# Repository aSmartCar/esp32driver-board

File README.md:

# ESP32Driver

This project is part of the ASV system and includes the custom PCB

## Specs
- Powersupply: 5.5 V - 36 V (depends on the voltage resistors)
- Microcontroller: ESP32
- USB to UART: FTDI FT231XQ
- Motorcontroller: Sparkfun DUALTB6612FNG

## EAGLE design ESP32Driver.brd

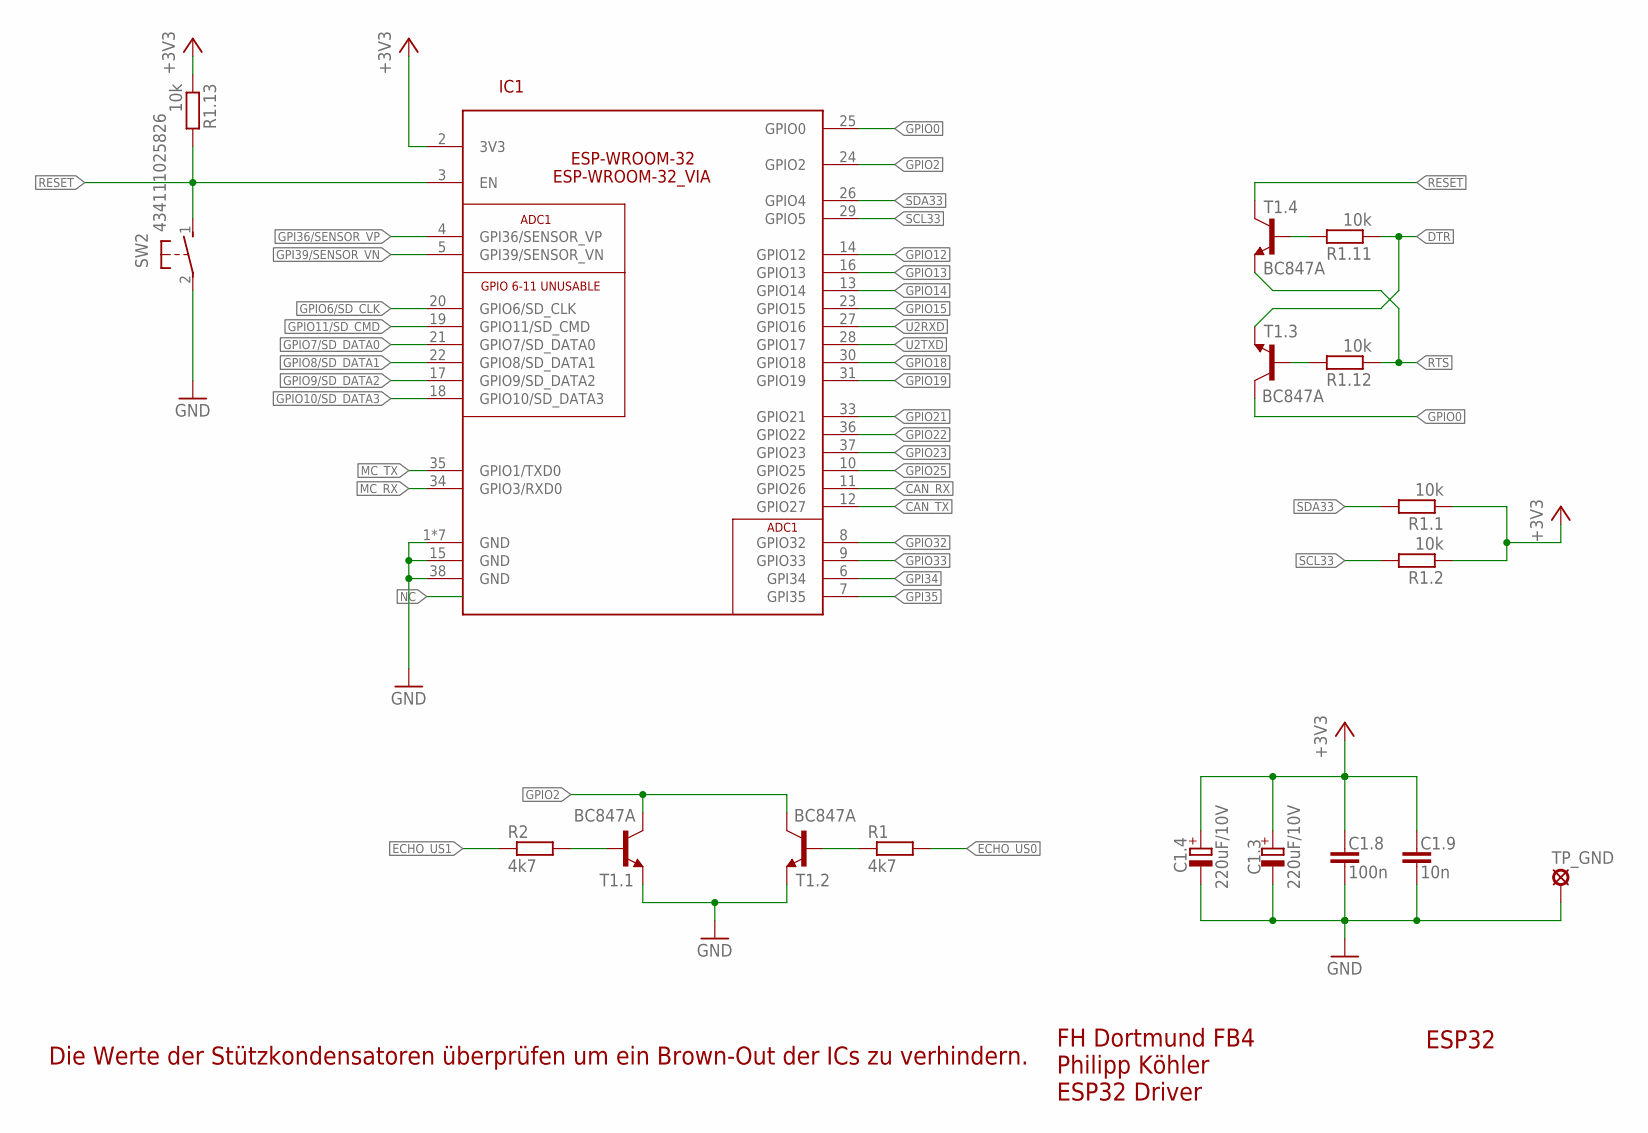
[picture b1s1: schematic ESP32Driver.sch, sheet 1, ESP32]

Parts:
C1.3, C1.4: 220uF/10V; SMC_C
C1.8: 100n; C0805
C1.9: 10n; C0805
IC1: ESP-WROOM-32_VIA; ESP-WROOM-32-VIA
R1, R2: 4k7; R0603
R1.1, R1.2, R1.11, R1.12, R1.13: 10k; R0805
SW2: 434111025826; 434121025816
T1.1, T1.2, T1.3, T1.4: BC847A; SOT23
TP_GND: GND; LSP10

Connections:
+3V3: C1.3.+, C1.4.+, C1.8.1, C1.9.1, IC1.2 (3V3), R1.1.1, R1.2.1, R1.13.1; also elsewhere on the board
CAN_RX: IC1.11 (GPIO26); also elsewhere on the board
CAN_TX: IC1.12 (GPIO27); also elsewhere on the board
DTR: R1.11.1, T1.3.2 (E); also elsewhere on the board
ECHO_US0: R1.2; also elsewhere on the board
ECHO_US1: R2.1; also elsewhere on the board
GND: C1.3.-, C1.4.-, C1.8.2, C1.9.2, IC1.1 (GND), IC1.15 (GND), IC1.38 (GND), IC1.THERMAL (GND), IC1.THERMAL1 (GND), IC1.T_VIA1 (GND), IC1.T_VIA2 (GND), IC1.T_VIA3 (GND), IC1.T_VIA4 (GND), SW2.2, T1.1.2 (E), T1.2.2 (E), TP_GND.MP; also elsewhere on the board
GPI34: IC1.6 (GPI34); also elsewhere on the board
GPI35: IC1.7 (GPI35); also elsewhere on the board
GPI36/SENSOR_VP: IC1.4 (GPI36/SENSOR_VP); also elsewhere on the board
GPI39/SENSOR_VN: IC1.5 (GPI39/SENSOR_VN); also elsewhere on the board
GPIO0: IC1.25 (GPIO0), T1.3.3 (C); also elsewhere on the board
GPIO2: IC1.24 (GPIO2), T1.1.3 (C), T1.2.3 (C)
GPIO6/SD_CLK: IC1.20 (GPIO6/SD_CLK)
GPIO7/SD_DATA0: IC1.21 (GPIO7/SD_DATA0)
GPIO8/SD_DATA1: IC1.22 (GPIO8/SD_DATA1)
GPIO9/SD_DATA2: IC1.17 (GPIO9/SD_DATA2)
GPIO10/SD_DATA3: IC1.18 (GPIO10/SD_DATA3)
GPIO11/SD_CMD: IC1.19 (GPIO11/SD_CMD)
GPIO12: IC1.14 (GPIO12); also elsewhere on the board
GPIO13: IC1.16 (GPIO13); also elsewhere on the board
GPIO14: IC1.13 (GPIO14); also elsewhere on the board
GPIO15: IC1.23 (GPIO15); also elsewhere on the board
GPIO18: IC1.30 (GPIO18); also elsewhere on the board
GPIO19: IC1.31 (GPIO19); also elsewhere on the board
GPIO21: IC1.33 (GPIO21); also elsewhere on the board
GPIO22: IC1.36 (GPIO22); also elsewhere on the board
GPIO23: IC1.37 (GPIO23); also elsewhere on the board
GPIO25: IC1.10 (GPIO25); also elsewhere on the board
GPIO32: IC1.8 (GPIO32); also elsewhere on the board
GPIO33: IC1.9 (GPIO33); also elsewhere on the board
MC_RX: IC1.34 (GPIO3/RXD0); also elsewhere on the board
MC_TX: IC1.35 (GPIO1/TXD0); also elsewhere on the board
unnamed: R1.1, T1.2.1 (B)
unnamed: R2.2, T1.1.1 (B)
unnamed: R1.12.2, T1.3.1 (B)
unnamed: R1.11.2, T1.4.1 (B)
NC: IC1.32 (NC)
RESET: IC1.3 (EN), R1.13.2, SW2.1, T1.4.3 (C)
RTS: R1.12.1, T1.4.2 (E); also elsewhere on the board
SCL33: IC1.29 (GPIO5), R1.2.2; also elsewhere on the board
SDA33: IC1.26 (GPIO4), R1.1.2; also elsewhere on the board
U2RXD: IC1.27 (GPIO16); also elsewhere on the board
U2TXD: IC1.28 (GPIO17); also elsewhere on the board

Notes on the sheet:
Die Werte der Stützkondensatoren überprüfen um ein Brown-Out der ICs zu verhindern.
GPIO 6-11 UNUSABLE
ESP32
FH Dortmund FB4 Philipp Köhler ESP32 Driver
ADC1

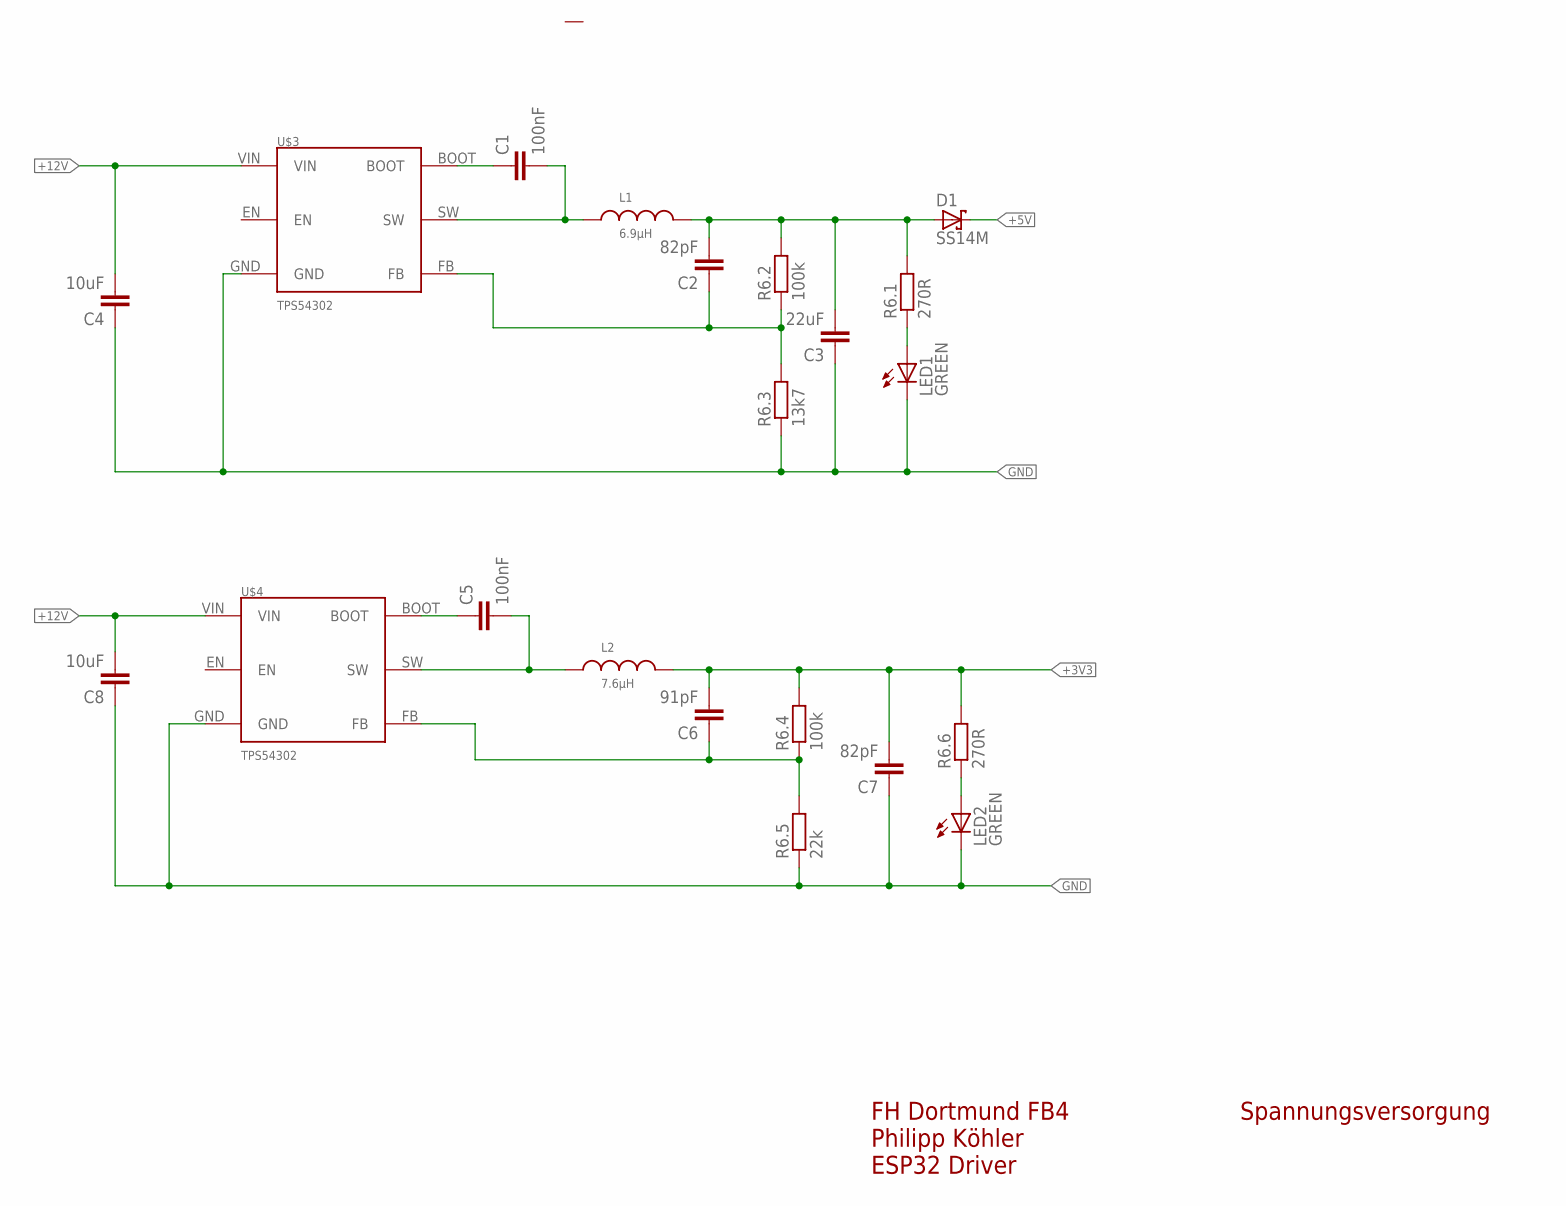
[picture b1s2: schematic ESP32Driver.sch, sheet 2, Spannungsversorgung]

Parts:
C1, C5: 100nF; C0805
C2, C7: 82pF; C0805
C3: 22uF; C0805
C4, C8: 10uF; C0805
C6: 91pF; C0805
D1: SS14M; MICRO-SMA
L1: 6.9µH; WE-HCI_7030/7040/7050
L2: 7.6µH; WE-HCI_7030/7040/7050
LED1, LED2: GREEN; SML0805
R6.1, R6.6: 270R; R0805
R6.2, R6.4: 100k; R0805
R6.3: 13k7; R0805
R6.5: 22k; R0805
U$3, U$4: TPS54302; SOT95P280X110-6

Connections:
+3V3: C6.2, C7.2, L2.2, R6.4.2, R6.6.2; also elsewhere on the board
+5V: D1.1 (C); also elsewhere on the board
+12V: C4.2, C8.2, U$3.VIN, U$4.VIN; also elsewhere on the board
GND: C3.1, C4.1, C7.1, C8.1, LED1.C, LED2.C, R6.3.1, R6.5.1, U$3.GND, U$4.GND; also elsewhere on the board
unnamed: C2.2, C3.2, D1.2 (A), L1.2, R6.1.2, R6.2.2
unnamed: C1.1, U$3.BOOT
unnamed: C1.2, L1.1, U$3.SW
unnamed: C2.1, R6.2.1, R6.3.2, U$3.FB
unnamed: C5.1, U$4.BOOT
unnamed: LED1.A, R6.1.1
unnamed: C5.2, L2.1, U$4.SW
unnamed: C6.1, R6.4.1, R6.5.2, U$4.FB
unnamed: LED2.A, R6.6.1

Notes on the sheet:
Spannungsversorgung
FH Dortmund FB4 Philipp Köhler ESP32 Driver

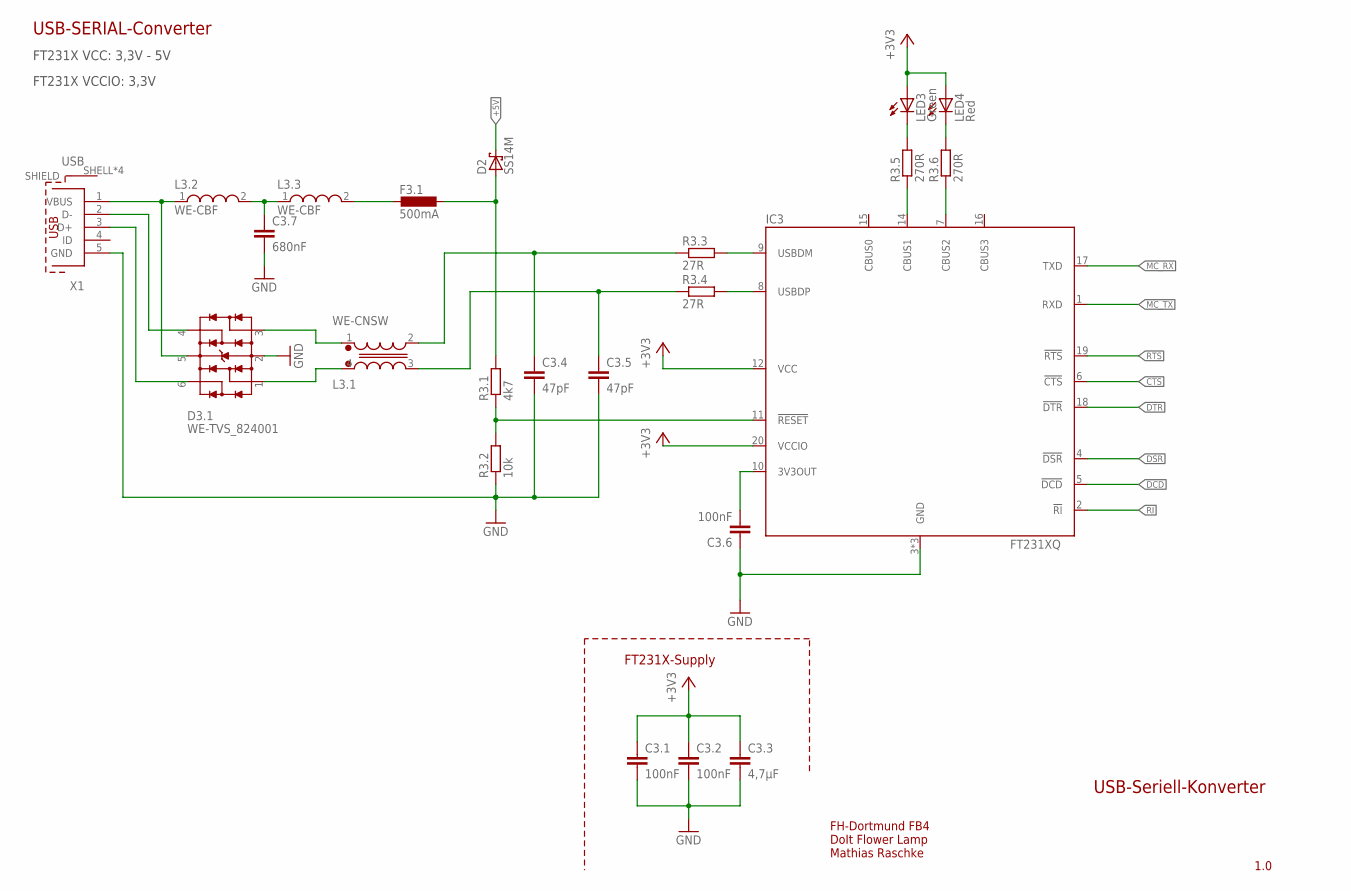
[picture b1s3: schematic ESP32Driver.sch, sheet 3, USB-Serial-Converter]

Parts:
C3.1, C3.2, C3.6: 100nF; C0603
C3.3: 4,7µF; C0805
C3.4, C3.5: 47pF; C0603
C3.7: 680nF; C0603
D2: SS14M; MICRO-SMA
D3.1: WE-TVS_824001; WE-TVS_SOT23-6L
F3.1: 500mA; L1812
IC3: FT231XQ; QFN20
L3.1: WE-CNSW; WE-CNSW_1206
L3.2, L3.3: WE-CBF; WE-CBF_0603(W=2.2)
LED3: Green; CHIPLED_0805
LED4: Red; CHIPLED_0805
R3.1: 4k7; R0603
R3.2: 10k; R0603
R3.3, R3.4: 27R; R0603
R3.5, R3.6: 270R; R0805
X1: USB; 629105136821

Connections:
3V3OUT: C3.6.2, IC3.10 (3V3OUT)
+3V3: C3.1.1, C3.2.1, C3.3.1, IC3.12 (VCC), IC3.20 (VCCIO), LED3.A, LED4.A; also elsewhere on the board
+5V: D2.1 (C); also elsewhere on the board
CTS: IC3.6 (!CTS)
DCD: IC3.5 (!DCD)
DSR: IC3.4 (!DSR)
DTR: IC3.18 (!DTR); also elsewhere on the board
GND: C3.1.2, C3.2.2, C3.3.2, C3.4.2, C3.5.2, C3.6.1, C3.7.2, D3.1.2 (GND), IC3.3 (GND), IC3.13 (GND), IC3.EXP (GND), R3.2.1, X1.5 (GND); also elsewhere on the board
MC_RX: IC3.17 (TXD); also elsewhere on the board
MC_TX: IC3.1 (RXD); also elsewhere on the board
unnamed: IC3.14 (CBUS1), R3.5.1
unnamed: IC3.7 (CBUS2), R3.6.1
unnamed: LED3.C, R3.5.2
unnamed: LED4.C, R3.6.2
unnamed: IC3.8 (USBDP), R3.4.2
unnamed: IC3.9 (USBDM), R3.3.2
unnamed: C3.5.1, L3.1.3 (2), R3.4.1
unnamed: C3.4.1, L3.1.2 (3), R3.3.1
unnamed: IC3.11 (!RESET), R3.1.1, R3.2.2
unnamed: D3.1.1, L3.1.4 (1)
unnamed: D3.1.3 (2), L3.1.1 (4)
unnamed: C3.7.1, L3.2.2, L3.3.1
unnamed: D3.1.5 (VDD), L3.2.1, X1.1 (VBUS)
unnamed: F3.1.2, L3.3.2
RI: IC3.2 (!RI)
RTS: IC3.19 (!RTS); also elsewhere on the board
VUSB: D2.2 (A), F3.1.1, R3.1.2
_N: D3.1.4 (3), X1.2 (D-)
_P: D3.1.6 (4), X1.3 (D+)

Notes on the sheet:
FT231X VCC: 3,3V - 5V
FT231X VCCIO: 3,3V
USB-SERIAL-Converter
FT231X-Supply
1.0
USB-Seriell-Konverter
FH-Dortmund FB4 DoIt Flower Lamp Mathias Raschke

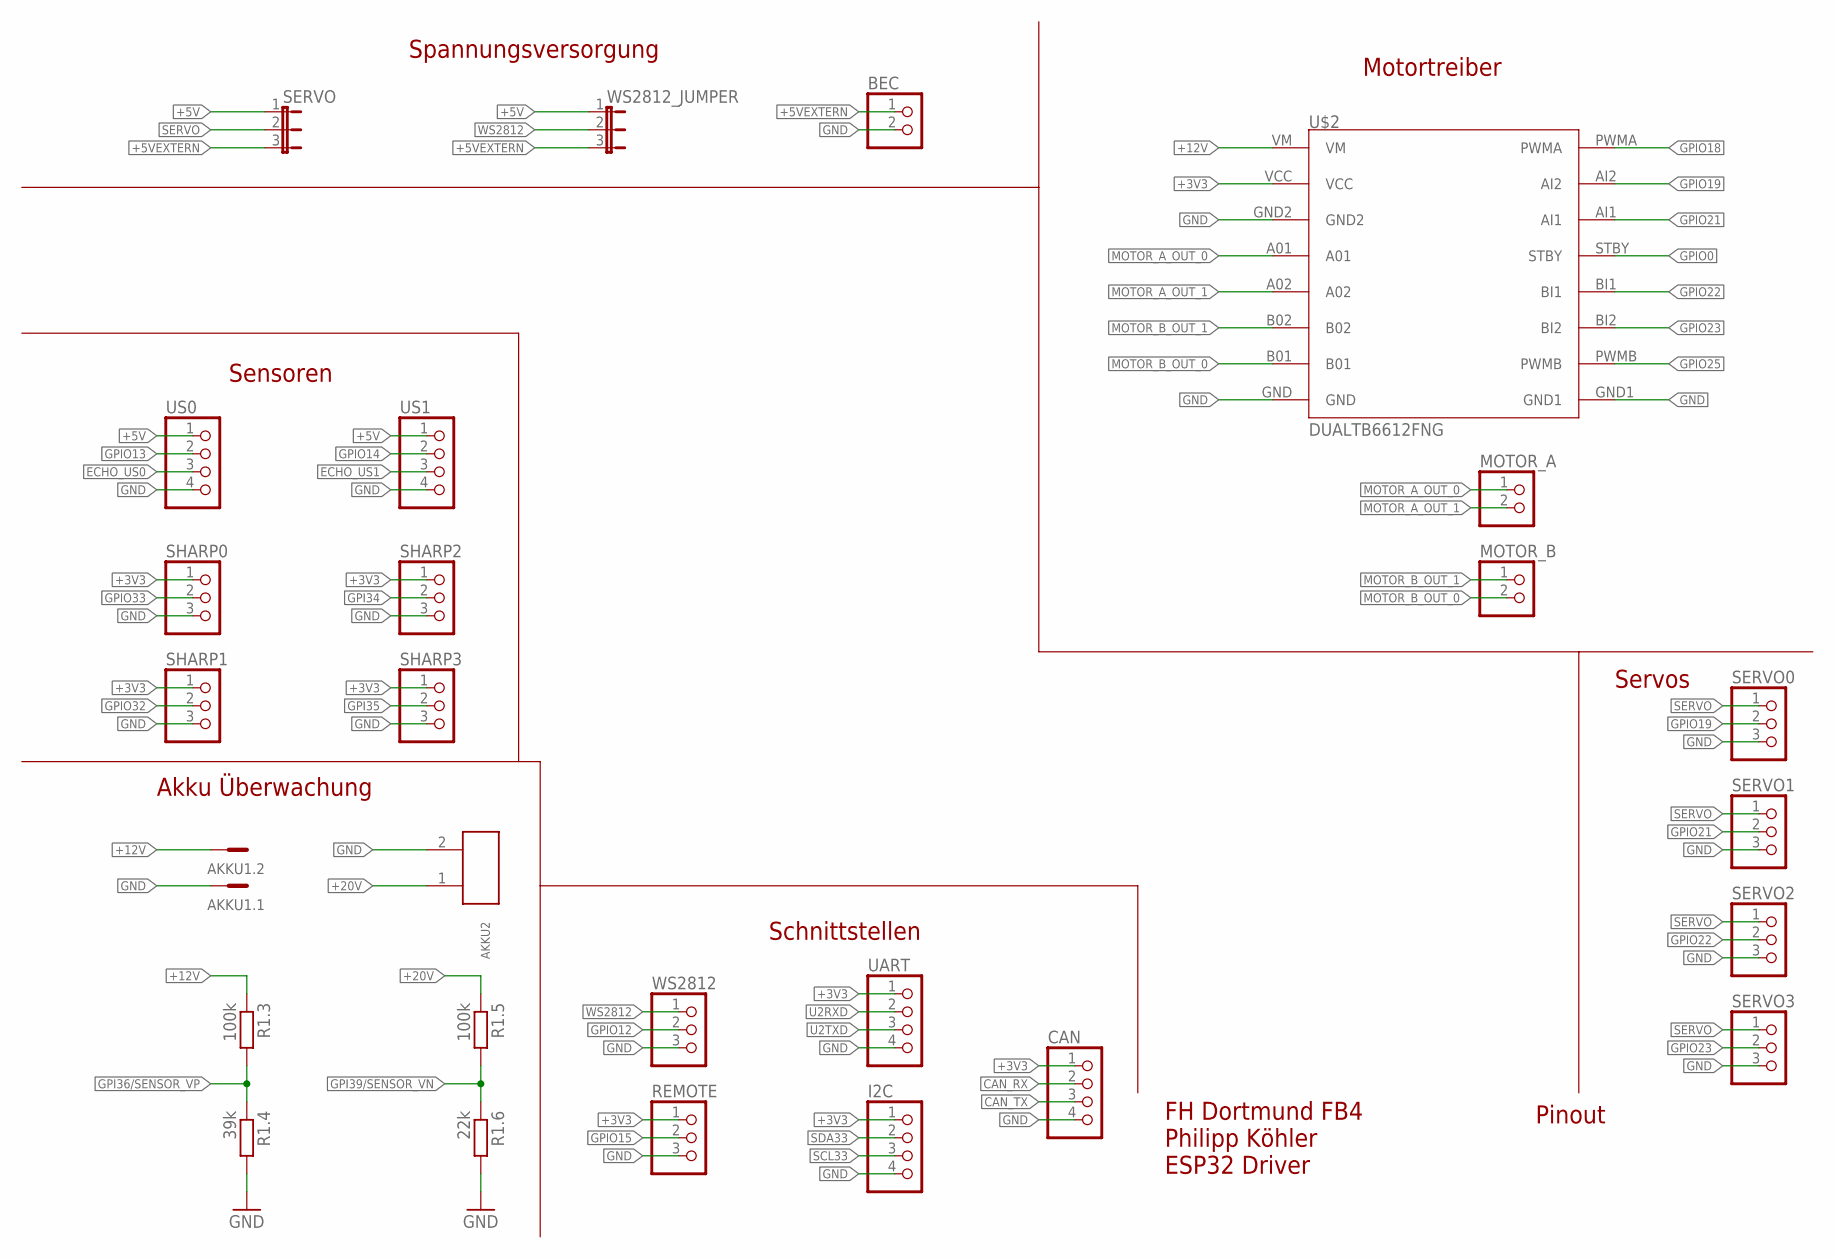
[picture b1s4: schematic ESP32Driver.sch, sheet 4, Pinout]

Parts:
AKKU1: RIA_382_02; 382_02
AKKU2: 620102131822
BEC: PINHD-1X2; 1X02
CAN: PINHD-1X4; 1X04
I2C: PINHD-1X4; 1X04
MOTOR_A: PINHD-1X2; 1X02
MOTOR_B: PINHD-1X2; 1X02
R1.3, R1.5: 100k; R0805
R1.4: 39k; R0805
R1.6: 22k; R0805
REMOTE: PINHD-1X3; 1X03
SERVO: JP2E; JP2
SERVO0, SERVO1, SERVO2, SERVO3: PINHD-1X3; 1X03
SHARP0, SHARP1, SHARP2, SHARP3: PINHD-1X3; 1X03
U$2: DUALTB6612FNG
UART: PINHD-1X4; 1X04
US0, US1: PINHD-1X4; 1X04
WS2812: PINHD-1X3; 1X03
WS2812_JUMPER: JP2E; JP2

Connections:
+3V3: CAN.1, I2C.1, REMOTE.1, SHARP0.1, SHARP1.1, SHARP2.1, SHARP3.1, U$2.VCC, UART.1; also elsewhere on the board
+5V: SERVO.1, US0.1, US1.1, WS2812_JUMPER.1; also elsewhere on the board
+5VEXTERN: BEC.1, SERVO.3, WS2812_JUMPER.3
+12V: AKKU1.2, R1.3.1, U$2.VM; also elsewhere on the board
+20V: AKKU2.1 (2), R1.5.1
CAN_RX: CAN.2; also elsewhere on the board
CAN_TX: CAN.3; also elsewhere on the board
ECHO_US0: US0.3; also elsewhere on the board
ECHO_US1: US1.3; also elsewhere on the board
GND: AKKU1.1, AKKU2.2 (1), BEC.2, CAN.4, I2C.4, R1.4.2, R1.6.2, REMOTE.3, SERVO0.3, SERVO1.3, SERVO2.3, SERVO3.3, SHARP0.3, SHARP1.3, SHARP2.3, SHARP3.3, U$2.GND, U$2.GND1, U$2.GND2, UART.4, US0.4, US1.4, WS2812.3; also elsewhere on the board
GPI34: SHARP2.2; also elsewhere on the board
GPI35: SHARP3.2; also elsewhere on the board
GPI36/SENSOR_VP: R1.3.2, R1.4.1; also elsewhere on the board
GPI39/SENSOR_VN: R1.5.2, R1.6.1; also elsewhere on the board
GPIO0: U$2.STBY; also elsewhere on the board
GPIO12: WS2812.2; also elsewhere on the board
GPIO13: US0.2; also elsewhere on the board
GPIO14: US1.2; also elsewhere on the board
GPIO15: REMOTE.2; also elsewhere on the board
GPIO18: U$2.PWMA; also elsewhere on the board
GPIO19: SERVO0.2, U$2.AI2; also elsewhere on the board
GPIO21: SERVO1.2, U$2.AI1; also elsewhere on the board
GPIO22: SERVO2.2, U$2.BI1; also elsewhere on the board
GPIO23: SERVO3.2, U$2.BI2; also elsewhere on the board
GPIO25: U$2.PWMB; also elsewhere on the board
GPIO32: SHARP1.2; also elsewhere on the board
GPIO33: SHARP0.2; also elsewhere on the board
MOTOR_A_OUT_0: MOTOR_A.1, U$2.A01
MOTOR_A_OUT_1: MOTOR_A.2, U$2.A02
MOTOR_B_OUT_0: MOTOR_B.2, U$2.B01
MOTOR_B_OUT_1: MOTOR_B.1, U$2.B02
SCL33: I2C.3; also elsewhere on the board
SDA33: I2C.2; also elsewhere on the board
SERVO: SERVO.2, SERVO0.1, SERVO1.1, SERVO2.1, SERVO3.1
U2RXD: UART.2; also elsewhere on the board
U2TXD: UART.3; also elsewhere on the board
WS2812: WS2812.1, WS2812_JUMPER.2

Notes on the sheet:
Pinout
Motortreiber
Servos
Spannungsversorgung
Akku Überwachung
Sensoren
Schnittstellen
FH Dortmund FB4 Philipp Köhler ESP32 Driver

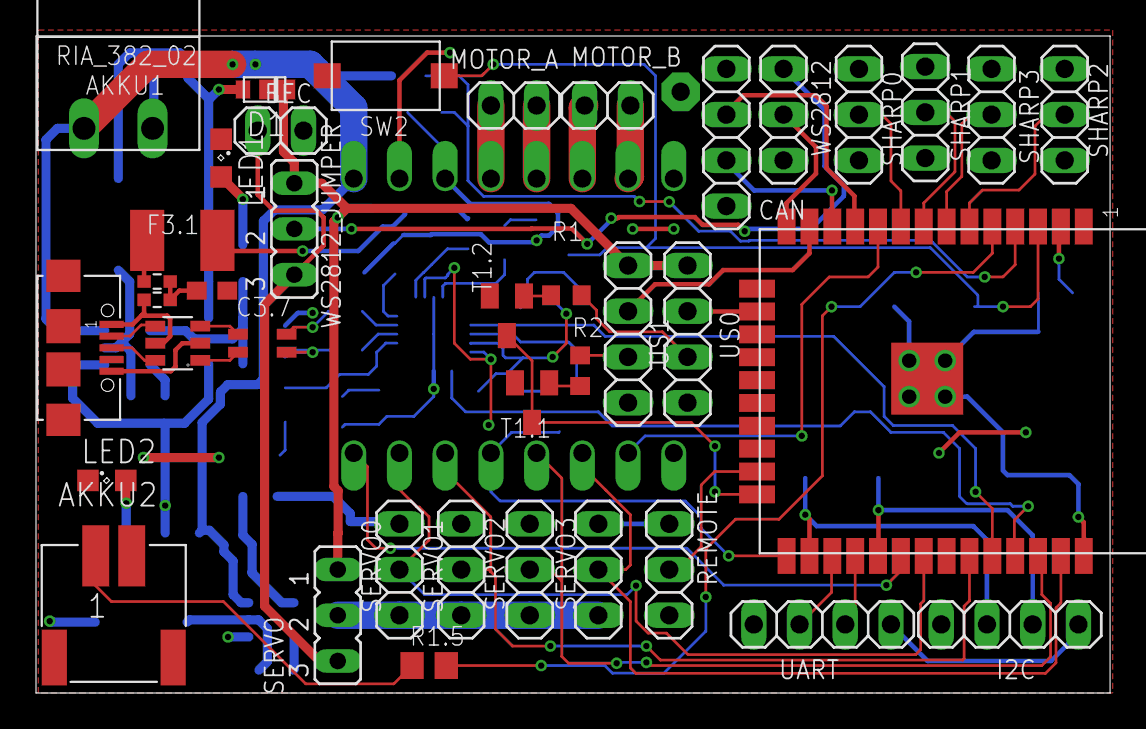
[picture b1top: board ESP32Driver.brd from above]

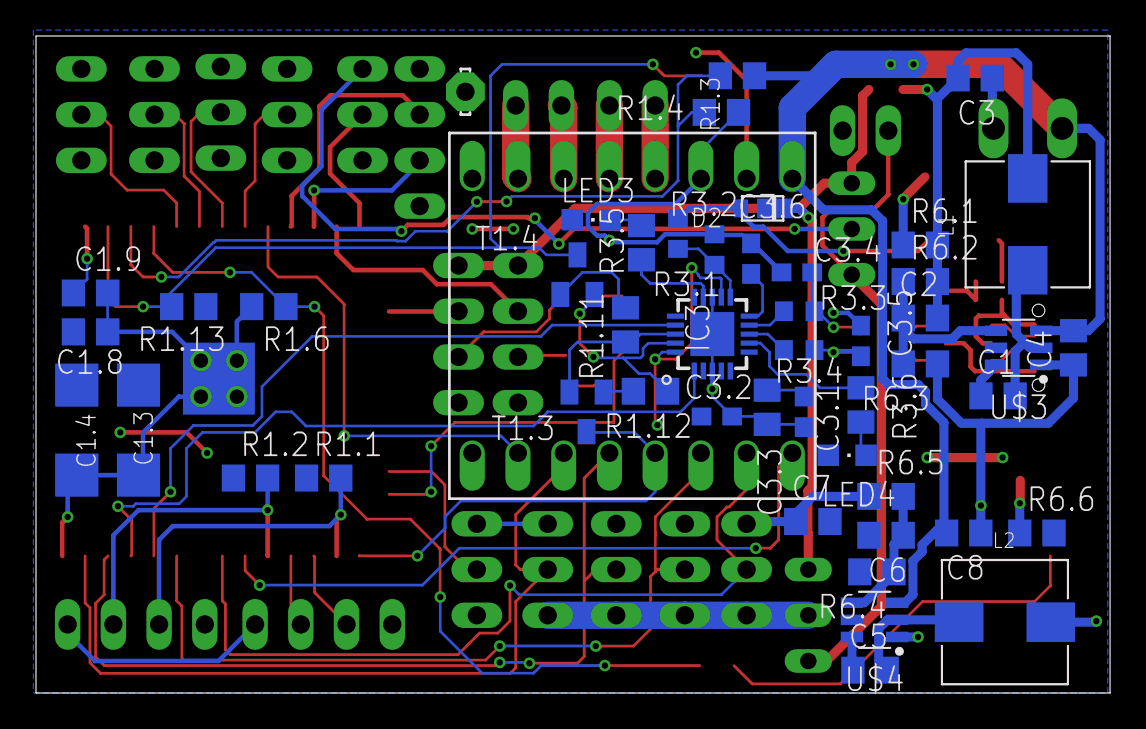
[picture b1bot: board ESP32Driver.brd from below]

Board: 2 copper layers, 59.7 x 36.5 mm, 89 parts (50 on the bottom side), 74 nets.

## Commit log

2020-09-15 Inital project commit

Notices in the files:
parts and their libraries:
Wurth_Elektronik_Passive_rev15d: Copyright: Würth Elektronik
